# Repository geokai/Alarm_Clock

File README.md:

# Alarm_Clock

Development of Arduino_Alarm_Clock repo - switched from Fritzing to Eagle PCB development tool.

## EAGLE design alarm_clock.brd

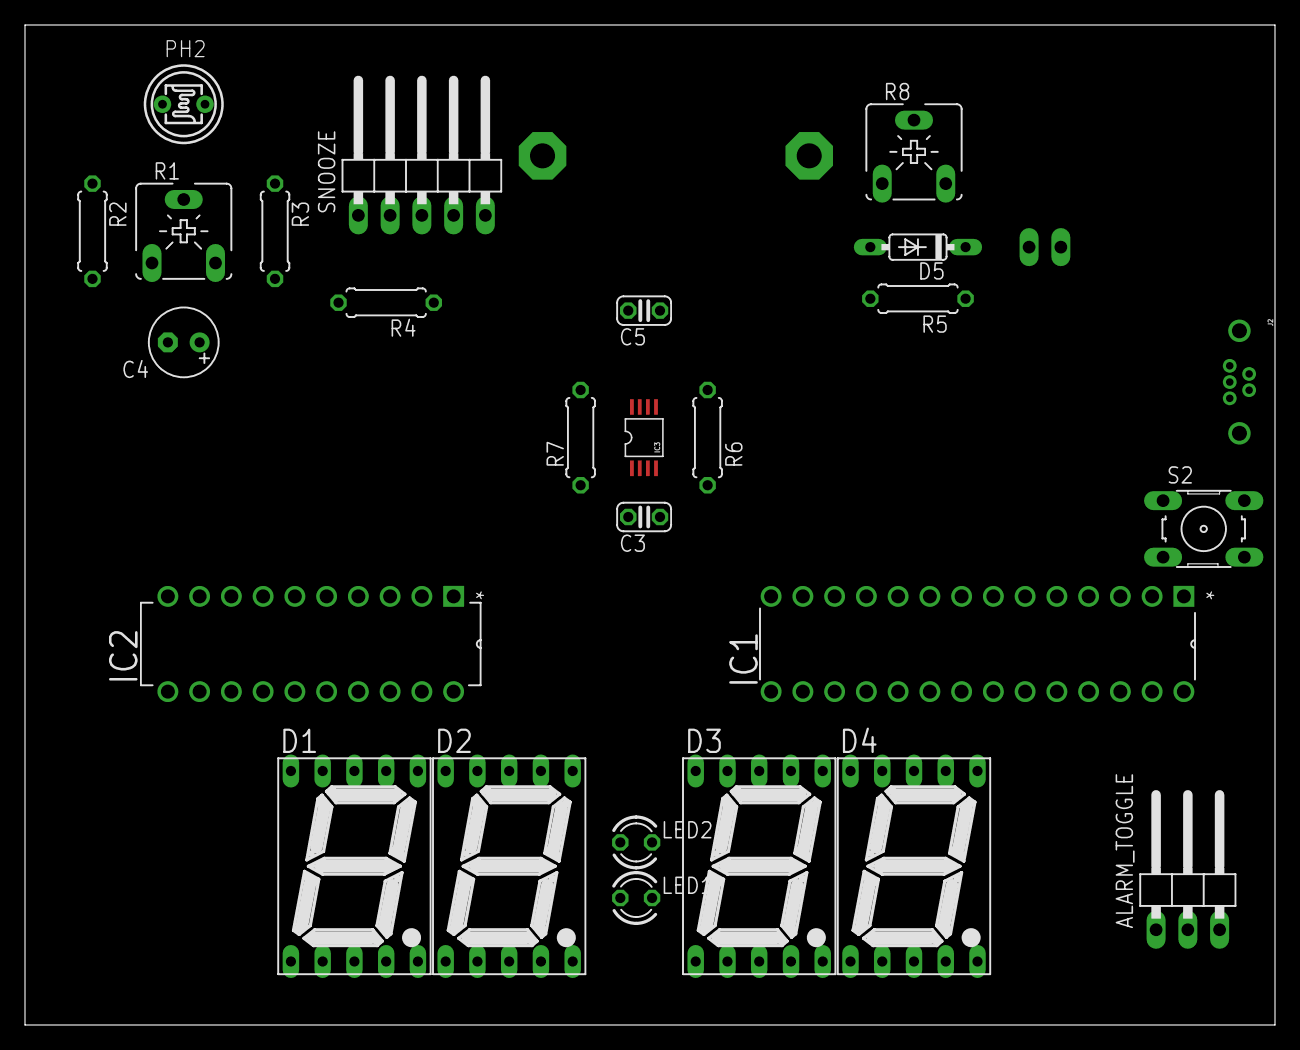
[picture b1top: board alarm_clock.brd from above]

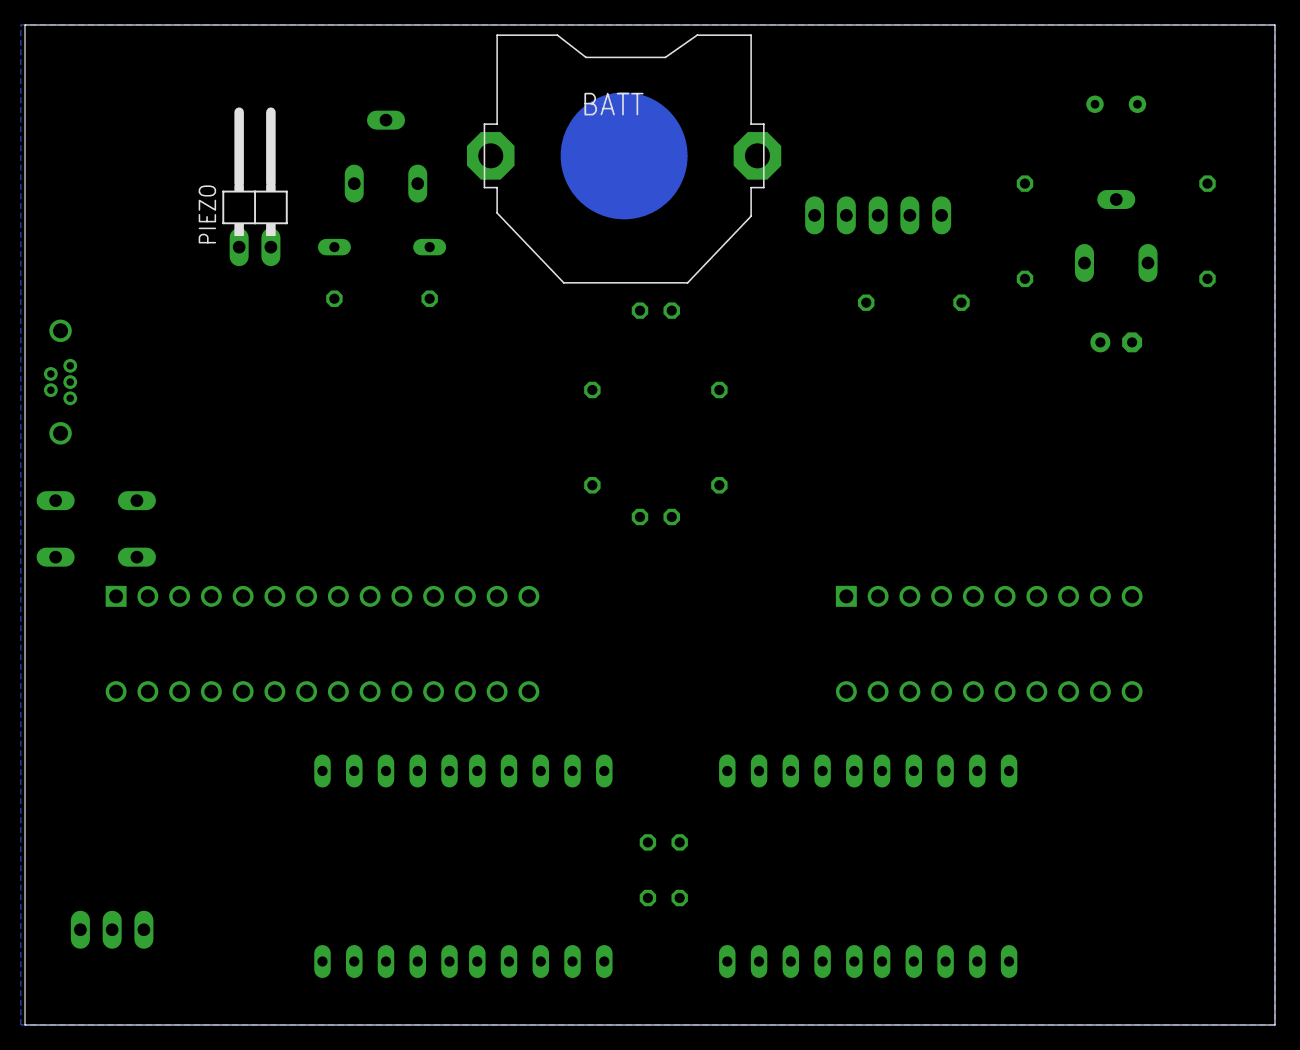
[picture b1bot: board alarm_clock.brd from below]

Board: 2 copper layers, 100.0 x 80.0 mm, 28 parts (2 on the bottom side), 32 nets, no tracks yet.

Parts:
ALARM_TOGGLE: 1X03/90
BATT: CR2032; CR2032-THRU
C3, C5: 1uF; C025-024X044
C4: 330uF; E2,5-6
D1, D2, D3, D4: 7SEG-13
D5: DO35-7
IC1: ATMEGA328P-PU; DIP254P762X457-28
IC2: MC14489BPE; DIP254P762X457-20
IC3: DS3231; DS3231-8_SO
J2: MICRO-B-TH
LED1, LED2: Orange; LED3MM
PH2: T0-46-A10XX
PIEZO: 1X02/90
R1: 10kΩ; CA6V
R2, R3, R4, R6, R7: 220Ω; 0207/7
R5: 1.5kΩ; 0207/7
R8: 10KΩ; CA6V
S2: B3F-10XX
SNOOZE: 1X05/90

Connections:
A: D1.7, D2.7, D3.7, D4.7, IC2.7, LED1.A, LED2.A
C: D1.4, D2.4, D3.4, D4.4, IC2.5
CLK: IC1.13, IC2.11
D: D1.2, D2.2, D3.2, D4.2, IC2.4
D1: D1.8, IC2.9
D2: D2.8, IC2.13
D3: D3.8, IC2.15
D4: D4.8, IC2.16
E: D1.1, D2.1, D3.1, D4.1, IC2.2
EN: IC1.6, IC2.10
F: D1.9, D2.9, D3.9, D4.9, IC2.1
G: D1.10, D2.10, D3.10, D4.10, IC2.20
GND: ALARM_TOGGLE.2, BATT.-, C3.2, C4.-, C5.2, D5.A, IC1.8, IC1.22, IC2.14, IC3.5, J2.5, J2.P$1, PH2.2, PIEZO.2, R2.1, S2.1, S2.2, SNOOZE.3
GREEN_LED: D1.6, D2.6, D3.6, D4.6, IC2.6, SNOOZE.4
LEDS: IC2.17, LED1.K, LED2.K
unnamed: R1.A, R2.2
unnamed: R4.2, SNOOZE.1
unnamed: R5.2, R8.S
unnamed: ALARM_TOGGLE.3, IC1.23
unnamed: ALARM_TOGGLE.1, IC1.24
unnamed: IC1.25, SNOOZE.2
unnamed: D5.C, PIEZO.1, R8.E
unnamed: C4.+, PH2.1, R1.S, R3.1
P: D1.5, D2.5, D3.5, D4.5, IC2.19
PZ: IC1.5, R5.1
RESET: IC1.1, S2.3
RX: IC2.8, R3.2
SCL: IC1.27, IC3.8, R7.2
SDA: IC1.28, IC3.7, R6.2
SNZ: IC1.11, R4.1
VBAT: BATT.+1, BATT.+2, C5.1, IC3.6
VCC: C3.1, IC1.7, IC1.20, IC2.3, IC3.2, J2.1, R6.1, R7.1

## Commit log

2016-08-26 [initial commit] gitignore file added:
2016-08-26 gitignore appended:
2016-08-26 gitignore amended:
2016-08-27 initial draft set-up:
2016-08-29 In progress save/commit:
2016-08-30 in progress commit:
2016-08-30 minor amandes:
2016-08-31 Adds pcb board file - initial:
2016-08-31 Adds '*.b#*' to gitignore file:
2016-08-31 Snooze LED and push-button omitted in lue of external, wired button with integral LED. Minor amends:
2016-09-02 Initial board set-up (no routes):
    Initial board set-up (pre route) with toggle switch on pcb and pin connectors
    shown on reverse side of board.
    Schematic amended accordingly.
2016-09-22 Shows battery holder mounted to reverse side of pcb:
2016-09-22 Replaced toggle switch & green led with connectors:
2016-12-18 'guide' layer made visible:
2016-12-25 crystal oscilator omitted form schematic/board:
    internal oscilator of atmega328p to be used ths reducing parts count:

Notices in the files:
parts and their libraries:
SparkFun-Connectors: Licensing: Creative Commons ShareAlike 4.0 International - https://creativecommons.org/licenses/by-sa/4.0
